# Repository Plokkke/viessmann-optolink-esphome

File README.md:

# viessmann-optolink-esphome

**Français** · [English](README.en.md)

Pilotez votre chaudière Viessmann depuis Home Assistant, grâce à une petite carte Wi-Fi qui se pose sur son port optique de diagnostic.

> [!NOTE]
> **État du projet.** Le firmware fonctionne sur la chaudière avec un prototype sur plaque d'essai. La carte et le boîtier sont finalisés ; leur version avec l'ESP32-C3 reste à valider sur la chaudière.
>
> **Cartes toutes faites.** J'ai peut-être des cartes montées en stock : ouvrez une *issue* si ça vous intéresse.

## Ce que ça permet

- **Suivre la chaudière** : températures (chaudière, eau chaude, extérieur, fumées), brûleur (marche, puissance, nombre de démarrages, heures de fonctionnement), pompes, défauts.
- **La régler depuis Home Assistant** :
  - consignes d'ambiance (normale et réduite) et d'eau chaude ;
  - mode de fonctionnement (arrêt, eau chaude seule, chauffage et eau chaude) et mode économie ;
  - courbe de chauffe.
- **Sans risque** : si Home Assistant ne répond plus pendant 30 minutes, la chaudière reprend son propre programme.

## Compatibilité

Testé sur une **Vitodens 222-W** avec régulation **Vitotronic 200 type HO1B**. Les autres chaudières Viessmann qui ont un port Optolink devraient fonctionner, en adaptant les adresses de la configuration. Les modèles sont listés sur le [wiki OpenV](https://github.com/openv/openv/wiki).

## Comment ça marche

Les régulations Viessmann ont en façade un port optique, l'Optolink, prévu pour les outils de diagnostic. Une LED infrarouge et un phototransistor, posés dessus, dialoguent avec la régulation. Un ESP32-C3 sous ESPHome relaie ces échanges vers Home Assistant en Wi-Fi. La carte s'alimente sur la sortie 230 V réservée aux accessoires de la chaudière.

```mermaid
flowchart LR
  HA[Home Assistant] <-- Wi-Fi --> C3[ESP32-C3<br>ESPHome]
  C3 <-- liaison série --> IR[LED IR +<br>phototransistor]
  IR <-- infrarouge --> OL[Optolink<br>de la Vitotronic]
  P96[Fiche 96<br>230 V] --> PSU[Alimentation isolée<br>230 V → 5 V] --> C3
```

## D'où ça vient

Le projet part du composant ESPHome `optolink` de [j0ta29](https://github.com/j0ta29) ([PR #4453](https://github.com/esphome/esphome/pull/4453), fermée par son auteur en octobre 2026 sans être intégrée à ESPHome). Sa page de documentation n'est plus en ligne. Une copie tirée de [Web Archive](https://web.archive.org/web/20251012034933/https://deploy-preview-2737--esphome.netlify.app/components/optolink) est rangée dans `knowledge/viessmann-optolink-esphome.pdf` : on y trouve le schéma d'origine de l'adaptateur infrarouge et sa configuration ESPHome.

Le firmware utilise aujourd'hui [esphome_vitohome](https://github.com/SoulSolistice/esphome_vitohome) de SoulSolistice, un composant ESPHome maintenu qui parle le même protocole et a été mis au point sur la même régulation.

Ce dépôt y ajoute une carte dédiée, avec son alimentation 230 V, et un boîtier qui se fixe sur l'Optolink.

## Le matériel

### Alimentation 230 V

La carte se branche sur la **fiche 96** de la Vitotronic, la sortie 230 V prévue pour les accessoires. Elle est commandée par l'interrupteur de la chaudière : la carte s'éteint avec elle.

- **Alimentation isolée** HLK-PM01 (230 V → 5 V, 3 W) : la partie basse tension est séparée du secteur.
- **Fusible T1A** temporisé, sur porte-fusible, et **varistance** contre les surtensions.
- **Bornier à vis** pour les fils L et N (0,75 mm² souple, avec embouts).
- Plus de **6 mm** entre le 230 V et la basse tension sur la carte.

> [!WARNING]
> Ce montage touche au 230 V de la chaudière. Couper le courant avant toute intervention, et ne jamais brancher l'USB du C3 quand la carte est sous tension : sa broche 5 V est reliée directement à l'USB et alimenterait l'ordinateur. En cas de doute, faites appel à un électricien.

### Schéma

### Carte

Circuit 2 couches de 74 × 35,5 mm, tout en composants traversants. Le C3 est enfiché sur des barrettes, et la tête infrarouge se raccorde par un câble JST : tout se démonte.

| Dessus | Dessous |
|---|---|
|  |  |

Le projet KiCad 10 est dans `hardware/`, consultable en ligne sur [KiCanvas](https://kicanvas.org/?github=https://github.com/Plokkke/viessmann-optolink-esphome/blob/main/hardware/heater-controller.kicad_sch).

### Boîtier

Imprimé en 3D en quatre pièces : deux demi-coques, un couvercle coulissant et la fiche qui se clipse sur l'Optolink. Les fichiers sont dans `enclosure/` : un STL par pièce, `print-setup.stl` avec les quatre pièces sur le plateau, et la source Fusion 360.

## Fabriquer la carte

Deux façons, avec les mêmes fichiers Gerber :

- **La souder soi-même** : JLCPCB fabrique le circuit, LCSC fournit les pièces.
- **La faire monter par JLCPCB** : il soude tout, il ne reste qu'à clipser le fusible.

`hardware/scripts/export.sh` produit dans `hardware/fabrication/` les Gerbers, le panier LCSC et les fichiers d'assemblage JLCPCB (BOM et CPL). Il faut KiCad 10.

**Prix de revient** (devis de novembre 2026) : pour 5 cartes, environ 60 $ de fabrication et de montage chez JLCPCB, plus environ 15 € de fusibles et de câbles, vendus par lots. L'impression du boîtier est négligeable (environ 1 € en fablab). Cela fait **14 à 17 € par carte**, mais **environ 70 €** pour une seule carte si l'on n'a pas déjà les pièces.

### Pièces pour une carte

| Pièce | Qté | Référence | Prix unitaire |
|---|---|---|---|
| Alimentation Hi-Link HLK-PM01 | 1 | LCSC C209903 | 2,74 $ |
| Porte-fusible TR5 Littelfuse 56000001009 | 1 | LCSC C142909 | 0,76 $ |
| Fusible TR5 T1A 250 V temporisé Littelfuse 37211000001 | 1 | LCSC C142808, DigiKey WK4248CT-ND | 0,22 $ (LCSC), 1,24 $ (DigiKey) |
| Varistance Bourns MOV-07D431K | 1 | LCSC C1528105 | 0,14 $ |
| Bornier à vis Kefa KF128 2 points, pas de 5,08 mm | 1 | LCSC C474952 | 0,19 $ |
| Embase JST PH 4 broches B4B-PH-K-S | 1 | LCSC C131334 | 0,05 $ |
| Barrette femelle 1×8, pas de 2,54 mm, 8,5 mm de haut | 2 | LCSC C27438 | — |
| Résistance 220 Ω 1/4 W | 1 | LCSC C57439 | — |
| Résistance 10 kΩ 1/4 W | 1 | LCSC C57436 | — |
| ESP32-C3 super mini, avec ses broches mâles | 1 | AliExpress | — |
| Câble JST PH 4 fils de 200 mm (Adafruit 4045) | 1 | DigiKey 1528-2825-ND | 0,95 $ |
| LED infrarouge 3 mm Everlight SIR204C | 1 | DigiKey 1080-1171-ND | 0,64 $ |
| Phototransistor 3 mm OSRAM SFH 309 FA | 1 | DigiKey 475-SFH309FA-ND | 0,55 $ |

Prix relevés en octobre et novembre 2026, à l'unité ou par petits lots.

## Installer

1. **Flasher le C3** par USB, hors de la carte (voir *Firmware*), puis l'enficher sur ses barrettes.
2. **Préparer la tête infrarouge** : souder la LED et le phototransistor au bout du câble JST, puis les enfoncer dans les trous de la fiche du boîtier. Sur J2 :
   - broche 1 : anode de la LED ;
   - broche 2 : cathode de la LED ;
   - broche 3 : collecteur du phototransistor ;
   - broche 4 : émetteur du phototransistor.

   Ne pas se fier aux couleurs du câble : repérer la broche 1 sur le connecteur.
3. **Câbler le 230 V**, chaudière coupée : les fils de la fiche 96 entrent par la fiche optique et se vissent sur le bornier (borne 1 : L, borne 2 : N).
4. **Fermer le boîtier** et le clipser sur l'Optolink, la LED en face du phototransistor de la chaudière (repère « V » de l'Optolink).
5. **Rallumer la chaudière** : la carte apparaît dans Home Assistant.

Pour vérifier que la LED émet, la regarder à travers l'appareil photo d'un téléphone.

## Firmware

Le firmware est une configuration ESPHome, dans `firmware/`.

```sh
uv tool install esphome
cp firmware/secrets.example.yaml firmware/secrets.yaml   # Wi-Fi, clé API, mot de passe OTA
cd firmware
esphome run controlleur-chaudiere.yaml --device /dev/cu.usbmodemXXXX    # premier flash, C3 en USB
esphome run controlleur-chaudiere.yaml --device controlleur-chaudiere.local   # mises à jour par Wi-Fi
```

Si le C3 n'apparaît pas en USB, le brancher en maintenant son bouton `BOOT`. `test-connectivity.yaml` remplace la chaudière par des entités factices, pour tester le Wi-Fi et Home Assistant sur table.

## Dans Home Assistant

La carte apparaît comme l'appareil **Controlleur chaudière**. Les principales entités :

| Entité | Usage |
|---|---|
| Boiler Temperature, Hot water temperature, Outdoor temperature | températures |
| Burner, Burner power, Burner starts, Burner hours | état et usage du brûleur |
| Disturbance, Last error | défaut en cours, dernière erreur avec sa date |
| Heating | thermostat : consigne d'ambiance et mode, en préréglages |
| Reduced room temperature setpoint | consigne d'ambiance réduite |
| Hot water setpoint | consigne d'eau chaude |
| Operation mode, Economy mode | mode de fonctionnement |
| Heating curve slope, Heating curve level | courbe de chauffe |

> [!IMPORTANT]
> La chaudière garde ses consignes et ses modes en mémoire EEPROM, qui s'use à chaque écriture. Dans vos automatisations, ne changez une valeur que lorsqu'elle doit vraiment changer : pas plus d'une fois toutes les 15 à 20 minutes, et jamais en boucle.

## Limites connues

- **Composant tiers** : le protocole Optolink n'est pas dans ESPHome ; il vient d'[esphome_vitohome](https://github.com/SoulSolistice/esphome_vitohome), figé sur sa version `v0.6`. Pour le mettre à jour, changer ce tag dans `firmware/controlleur-chaudiere.yaml` et recompiler.
- **Un seul pilote** : un autre thermostat branché sur la chaudière (Tado, Vitotrol…) réimpose sa propre consigne. Il faut le débrancher.
- **Wi-Fi** : l'antenne du C3 super mini est faible sur beaucoup de lots. Vérifier le signal (entité *Wi-Fi signal*) dans la chaufferie.

## Pour aller plus loin

- [`knowledge/architecture.md`](knowledge/architecture.md) : rôle de la carte dans la maison, règles d'écriture, choix de conception.
- [`knowledge/datapoints-optolink.md`](knowledge/datapoints-optolink.md) : adresses Optolink de la Vitotronic 200 HO1B.
- [`knowledge/pression-circuit-chauffage.md`](knowledge/pression-circuit-chauffage.md) : pression du circuit de chauffage.
- `knowledge/manuals/` : notices Viessmann.

## Licence

[MIT](LICENSE) : carte, boîtier et firmware sont libres de reproduction, de modification et de commercialisation.

---

**Mots-clés** : Viessmann Vitodens 222-W, Vitotronic 200 HO1B, chaudière gaz, Optolink, interface optique, adaptateur IR, Device ID `20CB`, protocole P300 / VS2, OpenV, vcontrold, ESPHome, Home Assistant, domotique, ESP32-C3, ESP32-C3 super mini, HLK-PM01, circuit imprimé KiCad, JLCPCB, boîtier imprimé en 3D, remplacement du thermostat Tado.

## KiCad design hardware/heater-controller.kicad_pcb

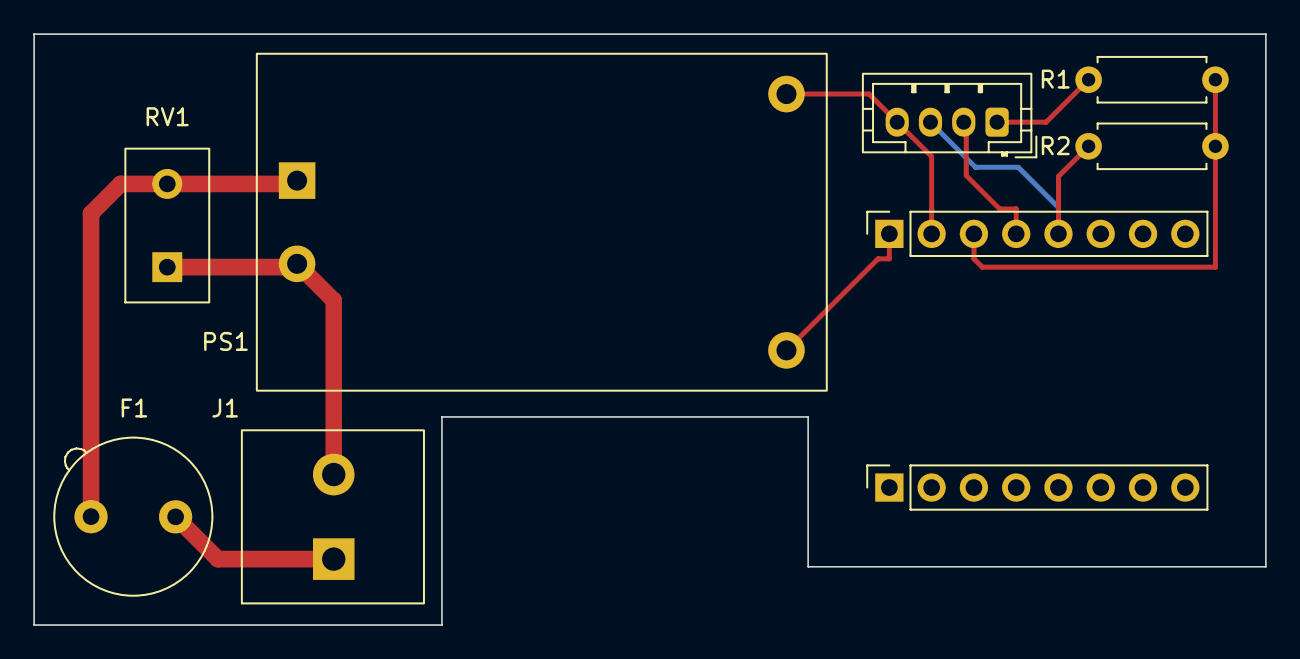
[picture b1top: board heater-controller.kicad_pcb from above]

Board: 2 copper layers, 74.0 x 35.5 mm, 10 parts (0 on the bottom side), 9 nets.

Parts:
F1: TR5 holder + T1A fuse; Fuseholder_TR5_Littelfuse_No560_No460
J1: KF128-5.08 (plug 96); TerminalBlock_Kefa_KF128-5.08_1x02
J2: JST B4B-PH-K (optical head); JST_PH_B4B-PH-K_1x04_P2.00mm_Vertical_Drill0.9
J3: Socket 1x8 THT (C3 pins 1-8); PinSocket_1x08_P2.54mm_Vertical
J4: Socket 1x8 THT (C3 pins 9-16); PinSocket_1x08_P2.54mm_Vertical
MOD1: ESP32-C3_SuperMini; ESP32-C3_SuperMini_Outline
PS1: HLK-PM01; Converter_ACDC_HLK-PM01
R1: 220; R_Axial_DIN0207_L6.3mm_D2.5mm_P7.62mm_Horizontal
R2: 10k; R_Axial_DIN0207_L6.3mm_D2.5mm_P7.62mm_Horizontal
RV1: MOV-07D431K (275VAC); RV_Disc_D9mm_W4.8mm_P5mm_Inline

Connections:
+5V: J3.1, PS1.4
/3V3: J3.3, R1.1, R2.1
/L: F1.1, J1.1
/LED_A: J2.1, R1.2
/L_FUSED: F1.2, PS1.1, RV1.2
/N: J1.2, PS1.2, RV1.1
/RX_GPIO3: J2.3, J3.5, R2.2
/TX_GPIO4: J2.2, J3.4
GND: J2.4, J3.2, PS1.3
